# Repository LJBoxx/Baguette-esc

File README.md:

# Baguette-ESC – Experimental Compact ESC Based on VESC

**BaguetteESC** is an open-source, compact Electronic Speed Controller (ESC) inspired by the VESC platform. It is designed to push boundaries in high-voltage motor control and explore innovative hardware concepts.  
⚠️ **Please note: this project is in a very early stage and has not yet been tested.** Use at your own risk.

---
## ❗ Liability Warning

⚠️ THIS PROJECT IS PROVIDED "AS IS", WITHOUT ANY EXPRESS OR IMPLIED WARRANTY.
I AM NOT RESPONSIBLE FOR ANY DAMAGE TO PERSONS, PROPERTY, OR EQUIPMENT RESULTING FROM THE USE, MISUSE, OR MALFUNCTION OF THIS HARDWARE OR SOFTWARE.

BY USING ANY PART OF THIS PROJECT, YOU AGREE TO ASSUME ALL RISK AND LIABILITY.

---

## 🚧 Project Status: Experimental & Untested

This ESC design has **not been tested** in hardware yet. Schematics, PCB layouts, and component choices are experimental and may contain errors.  
**Do not use this design in safety-critical or commercial applications.** Community feedback and contributions are welcome to bring it closer to working prototype status.

---

## 🔧 Key Features

- **120V Toll MOSFETs** – For exploring high-voltage BLDC control
- **Compact Dual-Board Aluminum PCB Powerstage** – Designed for heat dissipation in a minimal footprint
- **Phase Filters** – Included to reduce switching noise and improve signal integrity
- **BMI160 IMU** – Onboard sensor for potential inertial feedback and experimentation
- **Expansion Port for Bluetooth Module** – Optional wireless connectivity for future development

---

## 📁 Repository Structure

- `/hardware` – Schematics, PCB layout (KiCad), BOM, and Gerbers
- `/firmware` – Configuration files for VESC firmware compatibility (WIP)
- `/docs` – Additional notes, board assembly info, and future test logs

---

## 🧪 Goals

- Explore high-voltage ESC design with open documentation
- Keep the design compact while pushing thermal and electrical limits
- Provide a foundation for collaborative experimentation and learning

---

## 📥 Getting Started

1. **Clone the Repository**

   ```bash
   git clone https://github.com/LJBoxx/Baguette-esc.git
   cd Baguette-esc
   ```

2. **Review the Design Files**
   - Hardware located in `/hardware`
   - Firmware is not yet customized; expected to work with stock VESC firmware (further testing required)

3. **⚠️ Warning Before Building**
   - This design is **completely untested**
   Electrical, thermal, and functional characteristics are unverified
   - Proceed only if you're comfortable debugging hardware issues

---

## 📜 License

This project is licensed under the **CERN Open Hardware Licence Version 2 - Strongly Reciprocal (CERN-OHL-S)**.

> If you distribute modified versions or hardware based on this project, you must also share your changes under the same license.

See the [LICENSE](./LICENSE) file for full legal text.

---

## 🙏 Acknowledgements

Special thanks to [Benjamin Vedder](https://vesc-project.com/) and the entire VESC community for laying the foundation for open-source motor control.

---

## 🤝 Contributing

Contributions, reviews, and test results are *very* welcome. Open an issue or submit a pull request to help move the project forward.

---

**⚡ Hack carefully. Test responsibly. Share openly.**

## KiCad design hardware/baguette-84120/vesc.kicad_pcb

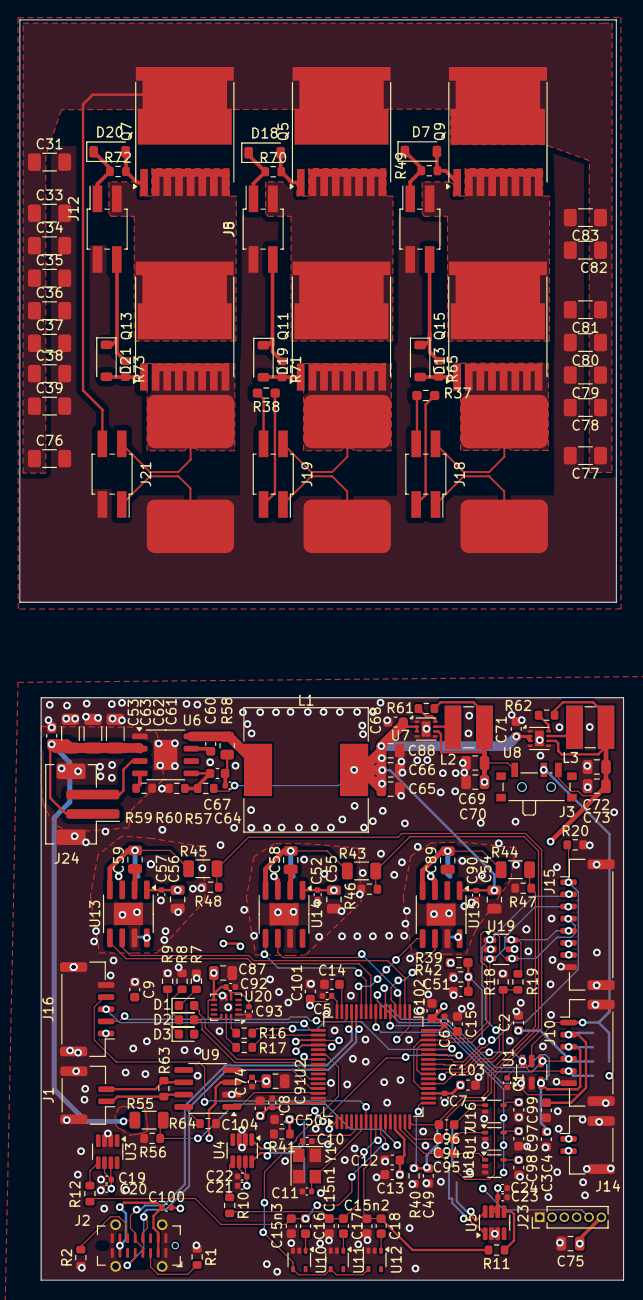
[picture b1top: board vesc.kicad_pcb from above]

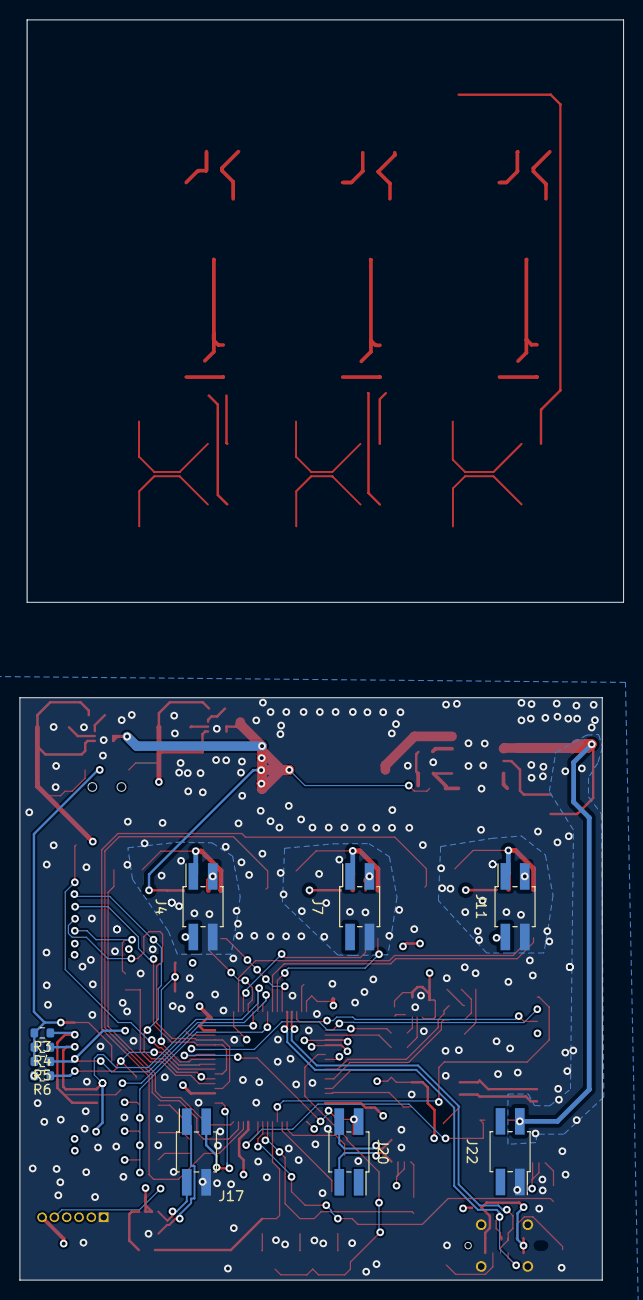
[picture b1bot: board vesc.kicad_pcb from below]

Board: 4 copper layers, 62.2 x 129.9 mm, 196 parts (10 on the bottom side), 116 nets.

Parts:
C1: 1n; C_0402_1005Metric
C2, C3, C4, C15n1, C15n2, C15n3: 1n; C_0603_1608Metric
C5, C6, C7, C8, C19, C20, C21, C22, C23, C24, C52, C57, C74, C90, C92, C93, C100: 100n; C_0402_1005Metric
C9, C94, C95, C96, C97, C98, C99: 100n; C_0603_1608Metric
C10, C11: 15p; C_0402_1005Metric
C12, C13, C14, C15, C101, C102, C103, C104: 2.2u; C_0603_1608Metric
C16, C17, C18: 15n; C_0603_1608Metric
C31, C33, C34, C35, C36, C37, C38, C39, C76, C77, C78, C79, C80, C81, C82, C83: C; C_1206_3216Metric_Pad1.33x1.80mm_HandSolder
C49, C50, C51: 2.2uf; C_0603_1608Metric
C53: 100n; C_0603_1608Metric_Pad1.08x0.95mm_HandSolder
C54, C55, C56, C58, C59, C89, C91: 4.7u; C_0805_2012Metric
C60: 2.2n; C_0603_1608Metric
C61, C62, C63: 1u; C_1206_3216Metric
C64: 1.2n; C_0402_1005Metric
C65, C66, C75, C87: 2.2u; C_0805_2012Metric
C67: 47p; C_0603_1608Metric
C68, C71: 10uF; C_0603_1608Metric
C69, C72: 22uF; C_0805_2012Metric
C70, C73: 10uF; C_0805_2012Metric
C88: 22u; C_0805_2012Metric
D1, D2, D3: LED; LED_0603_1608Metric
D7, D13, D18, D19, D20, D21: 1N4148W; D_SOD-123
J1, J14: Conn_01x02_Pin; JST_GH_BM02B-GHS-TBT_1x02-1MP_P1.25mm_Vertical
J2: USB_C_Receptacle_USB2.0; USB_C_Receptacle_G-Switch_GT-USB-7051x
J3: Conn_01x03_Pin; SW_SPDT_PCM12
J4, J7, J11: Conn_01x03_Socket; PinSocket_2x02_P2.00mm_Vertical_SMD
J5, J8: Conn_01x03_Pin; PinSocket_2x02_P2.00mm_Vertical_SMD
J10: Conn_01x06_Pin; JST_GH_BM06B-GHS-TBT_1x06-1MP_P1.25mm_Vertical
J12: Conn_01x0_Pin; PinSocket_2x02_P2.00mm_Vertical_SMD
J15: Conn_01x08_Pin; JST_GH_BM08B-GHS-TBT_1x08-1MP_P1.25mm_Vertical
J16: Conn_01x04_Pin; JST_GH_BM05B-GHS-TBT_1x05-1MP_P1.25mm_Vertical
J17, J20, J22: Conn_01x02_Socket; PinSocket_2x02_P2.00mm_Vertical_SMD
J18: Conn_01x04_Pin; PinSocket_2x02_P2.00mm_Vertical_SMD
J19, J21: Conn_01x02_Pin; PinSocket_2x02_P2.00mm_Vertical_SMD
J23: Conn_01x06_Pin; PinHeader_1x06_P1.27mm_Vertical
J24: Conn_01x02_Pin; JST_PH_B2B-PH-SM4-TB_1x02-1MP_P2.00mm_Vertical
L1: 220uh; L_SXN_SMDRI127
L2, L3: 10uH; L_Ferrocore_DLG-0403
Q5, Q7, Q9, Q11, Q13, Q15: NCEP028N12LL; Infineon_PG-HSOF-8-1
R1, R2: 5k1; R_0603_1608Metric
R3, R4, R5: 2k2; R_0603_1608Metric
R6, R40, R41, R42, R64: 10k; R_0603_1608Metric
R7, R8: 220; R_0603_1608Metric
R9, R10, R11, R12, R16, R17, R18, R19, R20: 1k; R_0603_1608Metric
R13, R14, R15: r; 5930-res
R37, R38, R39: 10k_NTC; R_0603_1608Metric_Pad0.98x0.95mm_HandSolder
R43, R44, R45, R55: 100K; R_1206_3216Metric
R46, R47, R48, R56: 2.2k; R_0603_1608Metric
R49, R65, R70, R71, R72, R73: 2r; R_0603_1608Metric
R57: 453k; R_0603_1608Metric
R58: 357k; R_0805_2012Metric
R59: 59k; R_0603_1608Metric
R60: 50k; R_0603_1608Metric
R61, R62: 100k; R_0603_1608Metric
R63: 120ohm; R_0603_1608Metric
U1, U19: SRV05-4; SOT-23-6
U2: STM32F405RGTx; LQFP-64_10x10mm_P0.5mm
U3, U4, U5: SOT-23-8
U6: LM5168F; HSOP-8-1EP_3.9x4.9mm_P1.27mm_EP2.41x3.1mm
U7: TPS62173DSG; WSON-8-1EP_2x2mm_P0.5mm_EP0.9x1.6mm
U8: TPS62172DSG; WSON-8-1EP_2x2mm_P0.5mm_EP0.9x1.6mm
U9: MCP2551-I-SN; SOIC-8_3.9x4.9mm_P1.27mm
U10, U11, U12, U16, U17, U18: MC74VHC1GT66; SOT-353_SC-70-5
U13, U14, U15: SOIC-8-1EP_3.9x4.9mm_P1.27mm_EP2.29x3mm
U20: BMI160; Bosch_LGA-14_3x2.5mm_P0.5mm
Y1: 8m; Crystal_SMD_3225-4Pin_3.2x2.5mm

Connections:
+3V3: C5.1, C6.1, C7.1, C8.1, C12.2, C13.2, C19.2, C20.2, C21.2, C22.2, C23.2, C24.2, C72.2, C73.2, C75.2, C87.2, C92.2, C93.2, C97.2, C98.2, C99.2, C101.2, C102.2, C103.2, C104.2, D3.2 (A), J3.3, J15.7, J16.1, J18.4, J19.3, J20.1, J23.6, L3.2, R6.2, R37.1, R38.1, R39.1, R62.2, U2.1 (VBAT), U2.13 (VDDA), U2.19 (VDD), U2.32 (VDD), U2.48 (VDD), U2.64 (VDD), U3.6 (Vs), U3.7 (REF1), U4.6 (Vs), U4.7 (REF1), U5.6 (Vs), U5.7 (REF1), U8.6 (VOS), U10.5 (V+), U11.5 (V+), U12.5 (V+), U16.5 (V+), U17.5 (V+), U18.5 (V+), U19.5 (VP), U20.5 (VDDIO), U20.8 (VDD), U20.12 (CSB)
+5V: C69.2, C70.2, C74.2, C91.2, C100.1, J3.1, J15.6, L2.2, R61.2, U7.6 (VOS), U9.3 (VDD)
+12V: C52.2, C54.2, C55.2, C56.2, C57.2, C64.1, C65.2, C66.2, C68.2, C71.2, C88.2, C90.2, L1.2, R57.1, U7.2 (VIN), U7.3 (EN), U8.2 (VIN), U8.3 (EN), U13.1 (VDD), U14.1 (VDD), U15.1 (VDD)
+BATT: C31.1, C33.1, C34.1, C35.1, C36.1, C37.1, C38.1, C39.1, C53.1, C61.2, C62.2, C63.2, C76.1, C77.1, C78.1, C79.1, C80.1, C81.1, C82.1, C83.1, J21.4, J22.2, J24.1, Q5.2 (D), Q7.2 (D), Q9.2 (D), R55.2, U6.2 (VIN)
/Drivers/Bin_A: U2.34 (PB13), U13.6 (lin)
/Drivers/Bin_B: U2.35 (PB14), U14.6 (lin)
/Drivers/Bin_C: U2.36 (PB15), U15.6 (lin)
/Drivers/G_B_A: J11.2, U13.8 (Lo)
/Drivers/G_B_B: J7.2, U14.8 (Lo)
/Drivers/G_B_C: J4.2, U15.8 (Lo)
/Drivers/G_T_A: J11.3, U13.3 (Ho)
/Drivers/G_T_B: J7.3, U14.3 (Ho)
/Drivers/G_T_C: J4.3, U15.3 (Ho)
/Drivers/PHASE_A: C59.1, J11.1, R45.2, U13.4 (Hs)
/Drivers/PHASE_B: C58.1, J7.1, R43.2, U14.4 (Hs)
/Drivers/PHASE_C: C89.1, J4.1, R44.2, U15.4 (Hs)
/Drivers/Sens1: C95.2, R45.1, R48.2, U2.14 (PA0)
/Drivers/Sens2: C94.2, R43.1, R46.2, U2.15 (PA1)
/Drivers/Sens3: C96.2, R44.1, R47.2, U2.16 (PA2)
/Drivers/Tin_A: U2.41 (PA8), U13.5 (hin)
/Drivers/Tin_B: U2.42 (PA9), U14.5 (hin)
/Drivers/Tin_C: U2.43 (PA10), U15.5 (hin)
/Drivers/sens supply: R55.1, R56.2, U2.11 (PC3)
/Drivers/sensfil: U2.40 (PC9), U16.4, U17.4, U18.4
/Fet/CURR_FILTER: U2.54 (PD2), U10.4, U11.4, U12.4
/Fet/GAB: D13.1 (K), J12.4, R65.1
/Fet/GAT: D7.1 (K), J12.1, R49.1
/Fet/GBB: D19.1 (K), J8.4, R71.1
/Fet/GBT: D18.1 (K), J8.1, R70.1
/Fet/GCB: D21.1 (K), J5.4, R73.1
/Fet/GCT: D20.1 (K), J5.1, R72.1
/Fet/PHASE_A: J12.3, Q7.3 (S), Q13.2 (D)
/Fet/PHASE_B: J8.3, Q5.3 (S), Q11.2 (D)
/Fet/PHASE_C: J5.3, Q9.3 (S), Q15.2 (D)
/Fet/SENSE_A: C15n2.1, C18.1, R11.2, U2.8 (PC0)
/Fet/SENSE_B: C15n1.1, C17.1, R10.2, U2.9 (PC1)
/Fet/SENSE_C: C15n3.1, C16.1, R12.2, U2.10 (PC2)
/Fet/TEMP: C49.1, J17.3, J18.3, R37.2, R40.1, U2.17 (PA3)
/Fet/TEMP1: C50.1, J19.4, J20.2, R38.2, R41.1, U2.27 (PB1)
/Fet/TEMP2: C51.1, R39.2, R42.1, U2.26 (PB0)
/IMU/scl: R17.2, U2.50 (PA15)
/IMU/sda: R16.2, U2.28 (PB2)
/can/CAN_RX: U2.61 (PB8), U9.4 (RXD)
/can/CAN_TX: U2.62 (PB9), U9.1 (TXD)
/can/canh: J1.1, R63.1, U9.7 (CANH)
/can/canl: J1.2, R63.2, U9.6 (CANL)
/mcu/ADC_15: J15.1, R20.1, U2.25 (PC5)
/mcu/LED_GREEN: D1.2 (A), U2.57 (PB5)
/mcu/LED_RED: D2.2 (A), U2.59 (PB7)
/mcu/NRF_swclk: J23.4, U2.55 (PB3)
/mcu/NRF_swdio: J23.5, U2.33 (PB12)
/mcu/NRST: C9.1, J16.4, U2.7 (NRST)
/mcu/SCK_ADC_EXT: R18.1, R19.1, U2.21 (PA5)
/mcu/SWCLK: J16.3, U2.49 (PA14)
/mcu/SWDIO: J16.2, U2.46 (PA13)
/mcu/USBD+: J2.A6 (D+), J2.B6 (D+), U2.45 (PA12)
/mcu/USBD-: J2.A7 (D-), J2.B7 (D-), U2.44 (PA11)
GND: C1.2, C2.2, C3.2, C4.2, C5.2, C6.2, C7.2, C8.2, C9.2, C10.1, C11.1, C12.1, C13.1, C14.1, C15.1, C15n1.2, C15n2.2, C15n3.2, C19.1, C20.1, C21.1, C22.1, C23.1, C24.1, C31.2, C33.2, C34.2, C35.2, C36.2, C37.2, C38.2, C39.2, C49.2, C50.2, C51.2, C52.1, C53.2, C54.1, C55.1, C56.1, C57.1, C61.1, C62.1, C63.1, C65.1, C66.1, C68.1, C69.1, C70.1, C71.1, C72.1, C73.1, C74.1, C75.1, C76.2, C77.2, C78.2, C79.2, C80.2, C81.2, C82.2, C83.2, C87.1, C88.1, C90.1, C91.1, C92.1, C93.1, C97.1, C98.1, C99.1, C101.1, C102.1, C103.1, C104.1, J1.MP, J2.A1 (GND), J2.A12 (GND), J2.B1 (GND), J2.B12 (GND), J2.S1 (SHIELD), J4.4, J5.2, J7.4, J8.2, J10.6, J10.MP, J11.4, J12.2, J14.MP, J15.8, J15.MP, J16.5, J16.MP, J17.4, J21.3, J22.1, J23.1, J24.MP, R1.1, R2.1, R7.1, R8.1, R9.1, R13.2, R14.2, R15.2, R18.2, R20.2, R40.2, R41.2, R42.2, R46.1, R47.1, R48.1, R56.1, R59.2, R60.2, R64.2, U1.2 (VN), U2.12 (VSSA), U2.18 (VSS), U2.60 (BOOT0), U2.63 (VSS), U3.2 (GND), U3.3 (REF2), U4.2 (GND), U4.3 (REF2), U5.2 (GND), U5.3 (REF2), U6.1 (GND), U6.9 (EP), U7.1 (PGND), U7.4 (AGND), U7.5 (FB), U7.9 (PAD), U8.1 (PGND), U8.4 (AGND), U8.5 (FB), U8.9 (PAD), U9.2 (VSS), U10.2, U10.3 (GND), U11.2, U11.3 (GND), U12.2, U12.3 (GND), U13.7 (gnd), U13.9 (gnd), U14.7 (gnd), U14.9 (gnd), U15.7 (gnd), U15.9 (gnd), U16.2, U16.3 (GND), U17.2, U17.3 (GND), U18.2, U18.3 (GND), U19.2 (VN), U20.1 (SDO), U20.6 (GNDIO), U20.7 (GND), Y1.2, Y1.4
H1: C4.1, J10.2, R3.1, U1.1 (IO1), U2.37 (PC6)
H2: C3.1, J10.3, R4.1, U1.3 (IO2), U2.38 (PC7)
H3: C2.1, J10.4, R5.1, U1.4 (IO3), U2.39 (PC8)
LINE: J3.2, J10.1, R3.2, R4.2, R5.2, U1.5 (VP)
unnamed: C16.2, U10.1
unnamed: C17.2, U11.1
unnamed: C18.2, U12.1
unnamed: C64.2, C67.2, R58.1
unnamed: C94.1, U17.1
unnamed: C95.1, U18.1
unnamed: C96.1, U16.1
unnamed: C100.2, J2.A4 (VBUS), J2.A9 (VBUS), J2.B4 (VBUS), J2.B9 (VBUS)
unnamed: D1.1 (K), R7.2
unnamed: D2.1 (K), R8.2
unnamed: D3.1 (K), R9.2
unnamed: D7.2 (A), Q7.1 (G), R49.2
unnamed: D13.2 (A), Q13.1 (G), R65.2
unnamed: D18.2 (A), Q5.1 (G), R70.2
unnamed: D19.2 (A), Q11.1 (G), R71.2
unnamed: D20.2 (A), Q9.1 (G), R72.2
unnamed: D21.2 (A), Q15.1 (G), R73.2
unnamed: J2.A5 (CC1), R1.2
unnamed: J2.B5 (CC2), R2.2
unnamed: J24.2, U6.3 (EN/UVLO)
unnamed: C15.2, U2.31 (VCAP_1)
unnamed: C14.2, U2.47 (VCAP_2)
unnamed: R12.1, U3.5 (OUT)
unnamed: R10.1, U4.5 (OUT)
unnamed: R11.1, U5.5 (OUT)
unnamed: C60.2, U6.7 (BST)
unnamed: C67.1, R57.2, R60.1, U6.5 (FB)
unnamed: R59.1, U6.4 (RT)
unnamed: C60.1, L1.1, R58.2, U6.8 (SW)
unnamed: R61.1, U7.8 (PG)
unnamed: L2.1, U7.7 (SW)
unnamed: R62.1, U8.8 (PG)
unnamed: L3.1, U8.7 (SW)
unnamed: R64.1, U9.8 (Rs)
unnamed: C59.2, U13.2 (Hb)
unnamed: C58.2, U14.2 (Hb)
unnamed: C89.2, U15.2 (Hb)
unnamed: R17.1, U20.13 (SCx)
unnamed: R16.1, U20.14 (SDx)
TM: C1.1, J10.5, R6.1, U1.6 (IO4), U2.24 (PC4)
adc1: J15.5, R19.2, U19.6 (IO4)
adc2: J15.2, U2.22 (PA6), U19.1 (IO1)
in_1_+: J21.1, J22.3, U3.8 (IN+)
in_1_-: J21.2, J22.4, Q13.3 (S), R14.1, U3.1 (IN-)
in_2_+: J19.1, J20.3, U4.8 (IN+)
in_2_-: J19.2, J20.4, Q11.3 (S), R13.1, U4.1 (IN-)
in_3_+: J17.2, J18.1, U5.8 (IN+)
in_3_-: J17.1, J18.2, Q15.3 (S), R15.1, U5.1 (IN-)
nrf_rx: J14.2, J23.2, U2.52 (PC11)
nrf_tx: J14.1, J23.3, U2.51 (PC10)
osc+: C10.2, U2.5 (PH0), Y1.1
osc-: C11.2, U2.6 (PH1), Y1.3
rx: J15.4, U2.20 (PA4), U2.30 (PB11), U19.4 (IO3)
tx: J15.3, U2.23 (PA7), U2.29 (PB10), U19.3 (IO2)

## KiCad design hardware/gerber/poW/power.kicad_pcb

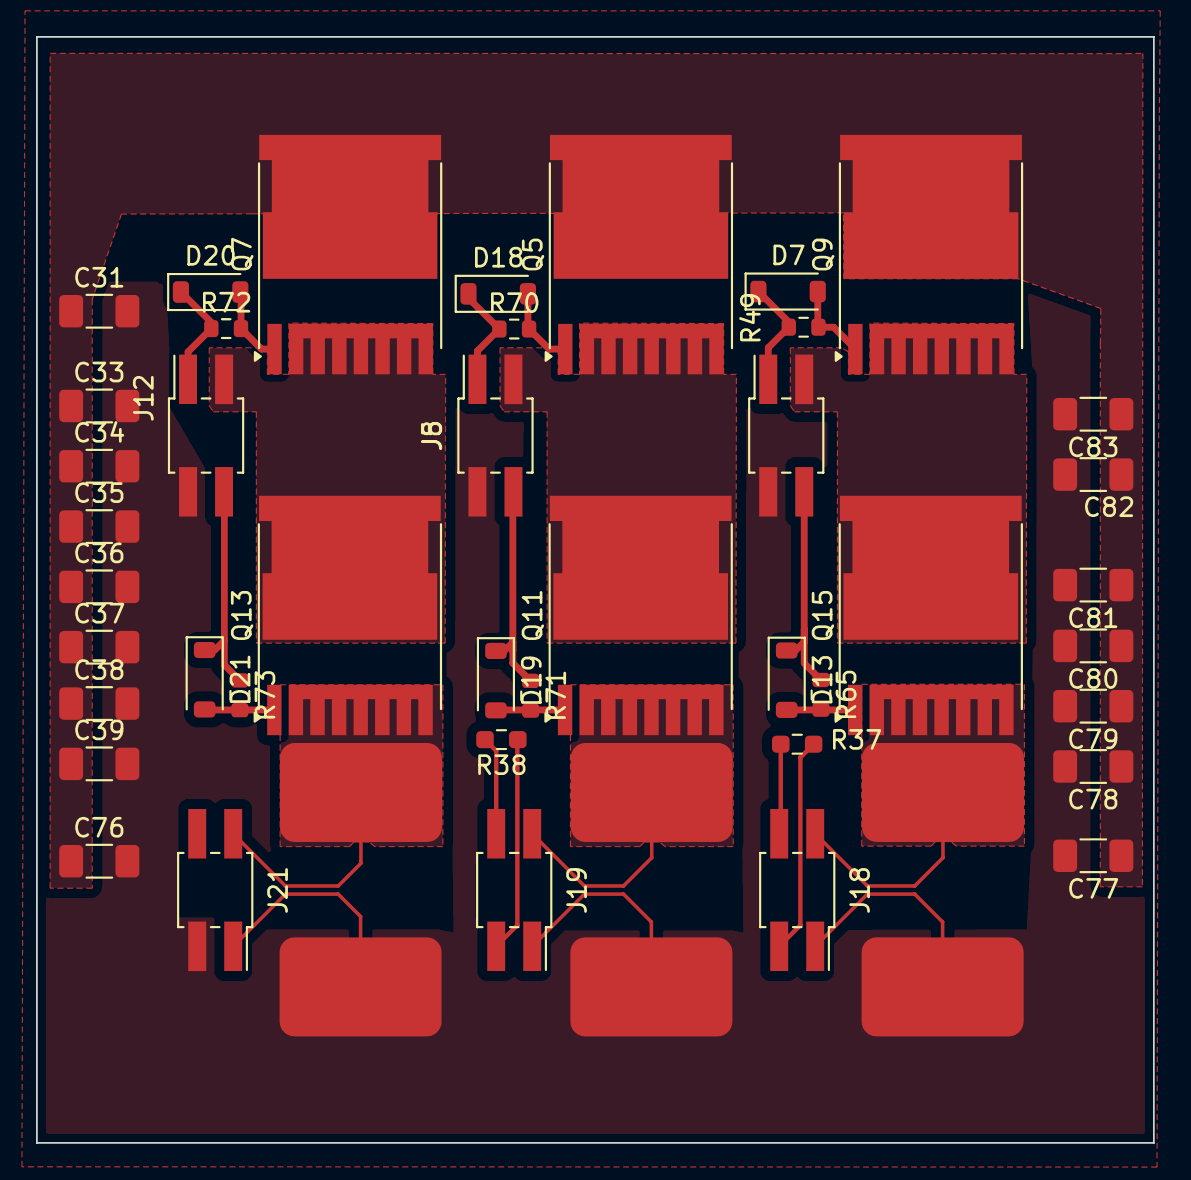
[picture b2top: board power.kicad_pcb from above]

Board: 4 copper layers, 62.1 x 61.4 mm, 45 parts (0 on the bottom side), 23 nets.

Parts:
C31, C33, C34, C35, C36, C37, C38, C39, C76, C77, C78, C79, C80, C81, C82, C83: C; C_1206_3216Metric_Pad1.33x1.80mm_HandSolder
D7, D13, D18, D19, D20, D21: 1N4148W; D_SOD-123
J5, J8: Conn_01x03_Pin; PinSocket_2x02_P2.00mm_Vertical_SMD
J12: Conn_01x0_Pin; PinSocket_2x02_P2.00mm_Vertical_SMD
J18: Conn_01x04_Pin; PinSocket_2x02_P2.00mm_Vertical_SMD
J19, J21: Conn_01x02_Pin; PinSocket_2x02_P2.00mm_Vertical_SMD
Q5, Q7, Q9, Q11, Q13, Q15: NCEP028N12LL; Infineon_PG-HSOF-8-1
R13, R14, R15: r; 5930-res
R37, R38: 10k_NTC; R_0603_1608Metric_Pad0.98x0.95mm_HandSolder
R49, R65, R70, R71, R72, R73: 2r; R_0603_1608Metric

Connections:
+3V3: J18.4, J19.3, R37.1, R38.1
+BATT: C31.1, C33.1, C34.1, C35.1, C36.1, C37.1, C38.1, C39.1, C76.1, C77.1, C78.1, C79.1, C80.1, C81.1, C82.1, C83.1, J21.4, Q5.2 (D), Q7.2 (D), Q9.2 (D)
/Fet/GAB: D13.1 (K), J5.4, R65.1
/Fet/GAT: D7.1 (K), J5.1, R49.1
/Fet/GBB: D19.1 (K), J8.4, R71.1
/Fet/GBT: D18.1 (K), J8.1, R70.1
/Fet/GCB: D21.1 (K), J12.4, R73.1
/Fet/GCT: D20.1 (K), J12.1, R72.1
/Fet/PHASE_A: J5.3, Q9.3 (S), Q15.2 (D)
/Fet/PHASE_B: J8.3, Q5.3 (S), Q11.2 (D)
/Fet/PHASE_C: J12.3, Q7.3 (S), Q13.2 (D)
/Fet/TEMP: J18.3, R37.2
/Fet/TEMP1: J19.4, R38.2
GND: C31.2, C33.2, C34.2, C35.2, C36.2, C37.2, C38.2, C39.2, C76.2, C77.2, C78.2, C79.2, C80.2, C81.2, C82.2, C83.2, J5.2, J8.2, J12.2, J21.3, R13.2, R14.2, R15.2
unnamed: D7.2 (A), Q9.1 (G), R49.2
unnamed: D13.2 (A), Q15.1 (G), R65.2
unnamed: D18.2 (A), Q5.1 (G), R70.2
unnamed: D19.2 (A), Q11.1 (G), R71.2
unnamed: D20.2 (A), Q7.1 (G), R72.2
unnamed: D21.2 (A), Q13.1 (G), R73.2
in_1_-: J18.2, Q15.3 (S), R15.1
in_2_-: J19.2, Q11.3 (S), R13.1
in_3_-: J21.2, Q13.3 (S), R14.1

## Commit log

2025-04-21 Update LICENSE
    oopsies pasted wrong license
2025-04-21 Add files via upload
    upload (messy) kicad files
2025-04-21 Update README.md
    i dont want to get sued..
2025-04-21 Add files via upload
    Picture
2025-04-21 Update README.md
    Add pic
2025-05-15 Update README.md
    Lmao chatgpt mistake
